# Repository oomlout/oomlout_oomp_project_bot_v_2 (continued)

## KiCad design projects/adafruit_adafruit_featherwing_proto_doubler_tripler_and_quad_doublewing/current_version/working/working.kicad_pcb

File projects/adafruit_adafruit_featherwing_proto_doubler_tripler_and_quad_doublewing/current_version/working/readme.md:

# adafruit_featherwing_proto_doubler_tripler_and_quad
 
## summary 
* id: adafruit_adafruit_featherwing_proto_doubler_tripler_and_quad_doublewing
* user: adafruit
* name: adafruit_featherwing_proto_doubler_tripler_and_quad
* board: doublewing
* repo: https://github.com/adafruit/Adafruit-FeatherWing-Proto-Doubler-Tripler-and-Quad

* src_file_repo_sch: 
* src_file_repo_sch_link: https://github.com/adafruit/Adafruit-FeatherWing-Proto-Doubler-Tripler-and-Quad/tree/master/
* full details link: https://github.com/oomlout/oomlout_oomp_project_bot_v_2/tree/main/projects/adafruit_adafruit_featherwing_proto_doubler_tripler_and_quad_doublewing/current_version/working  

## schematic  
  
[schematic (pdf)](working_schematic.pdf) 

## pcb  

[board (pdf)](working.pdf)  

## working_bom
| Id | Designator | Footprint | Quantity | Designation | Supplier and ref |  | None | 
| --- | --- | --- | --- | --- | --- | --- | --- | 
| 1 | MS1,MS2 | FEATHERWING_DIM | 2 | FEATHERWING_NODIM |  |  | [''] | 
| 2 | JP2,JP3 | 1X16_ROUND_76MIL | 2 |  |  |  | [''] | 
| 3 | JP1,JP4 | 1X12_ROUND_76MIL | 2 |  |  |  | [''] | 

## bom_schematic
| Ref | Qnty | Value | Cmp name | Footprint | Description | Vendor | DNP | 
| --- | --- | --- | --- | --- | --- | --- | --- | 
| JP1, JP4 | 2 | HEADER-1X1276MIL | HEADER-1X1276MIL | working:1X12_ROUND_76MIL |  |  |  | 
| JP2, JP3 | 2 | HEADER-1X16_76MIL | HEADER-1X16_76MIL | working:1X16_ROUND_76MIL |  |  |  | 
| MS1, MS2 | 2 | FEATHERWING_NODIM | FEATHERWING_NODIM | working:FEATHERWING_DIM |  |  |  |

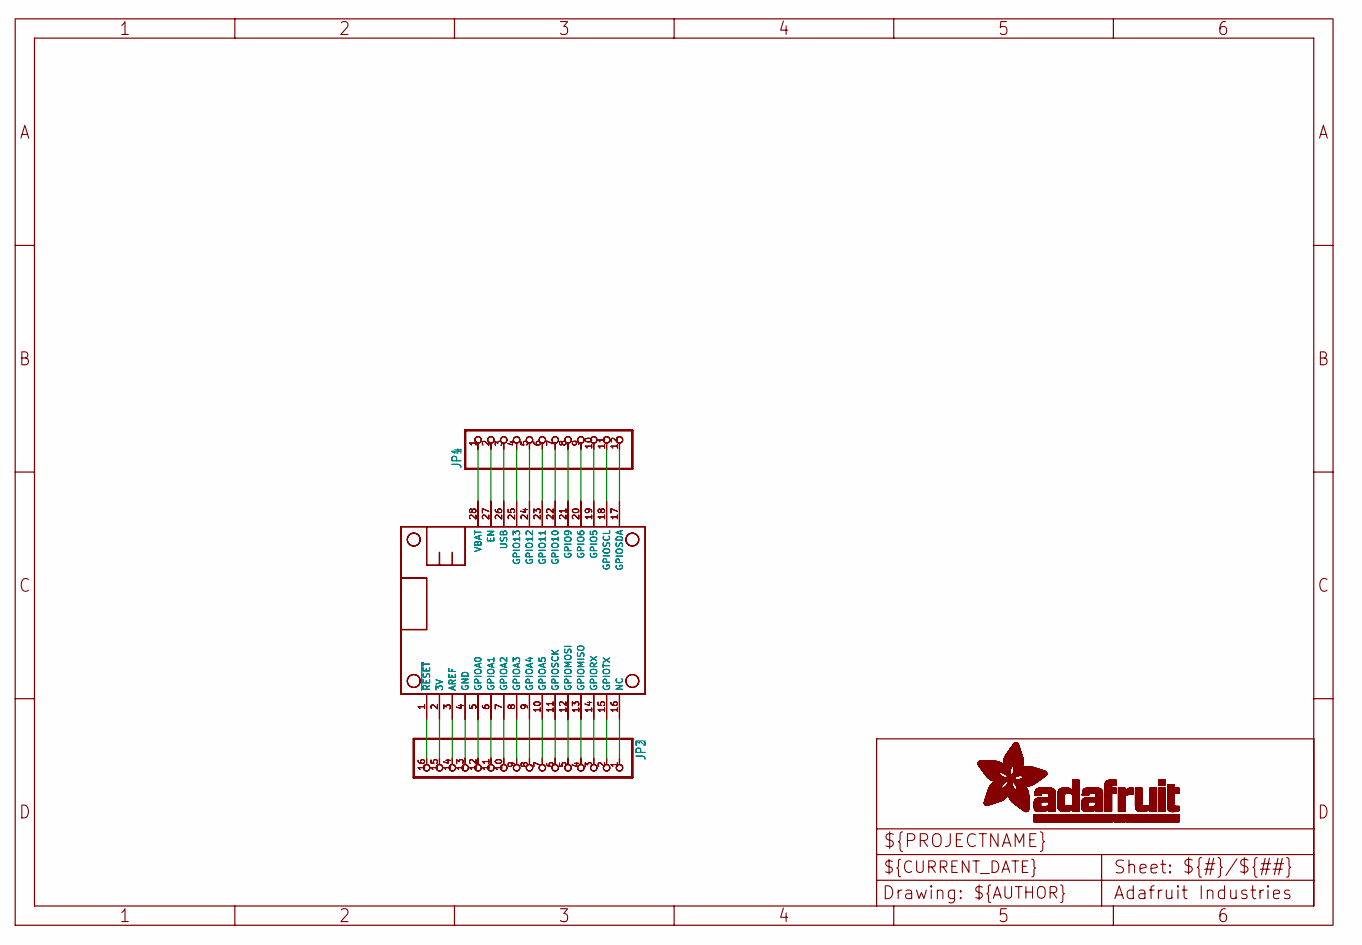
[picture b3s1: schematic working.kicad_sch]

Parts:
JP1, JP4: HEADER-1X1276MIL; 1X12_ROUND_76MIL
JP2, JP3: HEADER-1X16_76MIL; 1X16_ROUND_76MIL
MS1, MS2: FEATHERWING_NODIM; FEATHERWING_DIM

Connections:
3V: JP2.15, JP3.15, MS1.2 (3V), MS2.2 (3V)
GND: JP2.13, JP3.13, MS1.4 (GND), MS2.4 (GND)
unnamed: JP1.2, JP4.2, MS1.27 (EN), MS2.27 (EN)
unnamed: JP2.1, JP3.1, MS1.16 (NC), MS2.16 (NC)
unnamed: JP1.4, JP4.4, MS1.25 (GPIO13), MS2.25 (GPIO13)
unnamed: JP2.2, JP3.2, MS1.15 (GPIOTX), MS2.15 (GPIOTX)
unnamed: JP1.5, JP4.5, MS1.24 (GPIO12), MS2.24 (GPIO12)
unnamed: JP2.3, JP3.3, MS1.14 (GPIORX), MS2.14 (GPIORX)
unnamed: JP2.4, JP3.4, MS1.13 (GPIOMISO), MS2.13 (GPIOMISO)
unnamed: JP2.5, JP3.5, MS1.12 (GPIOMOSI), MS2.12 (GPIOMOSI)
unnamed: JP2.6, JP3.6, MS1.11 (GPIOSCK), MS2.11 (GPIOSCK)
unnamed: JP2.7, JP3.7, MS1.10 (GPIOA5), MS2.10 (GPIOA5)
unnamed: JP2.8, JP3.8, MS1.9 (GPIOA4), MS2.9 (GPIOA4)
unnamed: JP2.9, JP3.9, MS1.8 (GPIOA3), MS2.8 (GPIOA3)
unnamed: JP2.10, JP3.10, MS1.7 (GPIOA2), MS2.7 (GPIOA2)
unnamed: JP2.11, JP3.11, MS1.6 (GPIOA1), MS2.6 (GPIOA1)
unnamed: JP2.12, JP3.12, MS1.5 (GPIOA0), MS2.5 (GPIOA0)
unnamed: JP2.14, JP3.14, MS1.3 (AREF), MS2.3 (AREF)
unnamed: JP2.16, JP3.16, MS1.1 (~RESET), MS2.1 (~RESET)
unnamed: JP1.6, JP4.6, MS1.23 (GPIO11), MS2.23 (GPIO11)
unnamed: JP1.7, JP4.7, MS1.22 (GPIO10), MS2.22 (GPIO10)
unnamed: JP1.8, JP4.8, MS1.21 (GPIO9), MS2.21 (GPIO9)
unnamed: JP1.9, JP4.9, MS1.20 (GPIO6), MS2.20 (GPIO6)
unnamed: JP1.10, JP4.10, MS1.19 (GPIO5), MS2.19 (GPIO5)
unnamed: JP1.11, JP4.11, MS1.18 (GPIOSCL), MS2.18 (GPIOSCL)
unnamed: JP1.12, JP4.12, MS1.17 (GPIOSDA), MS2.17 (GPIOSDA)
USB: JP1.3, JP4.3, MS1.26 (USB), MS2.26 (USB)
VBAT: JP1.1, JP4.1, MS1.28 (VBAT), MS2.28 (VBAT)

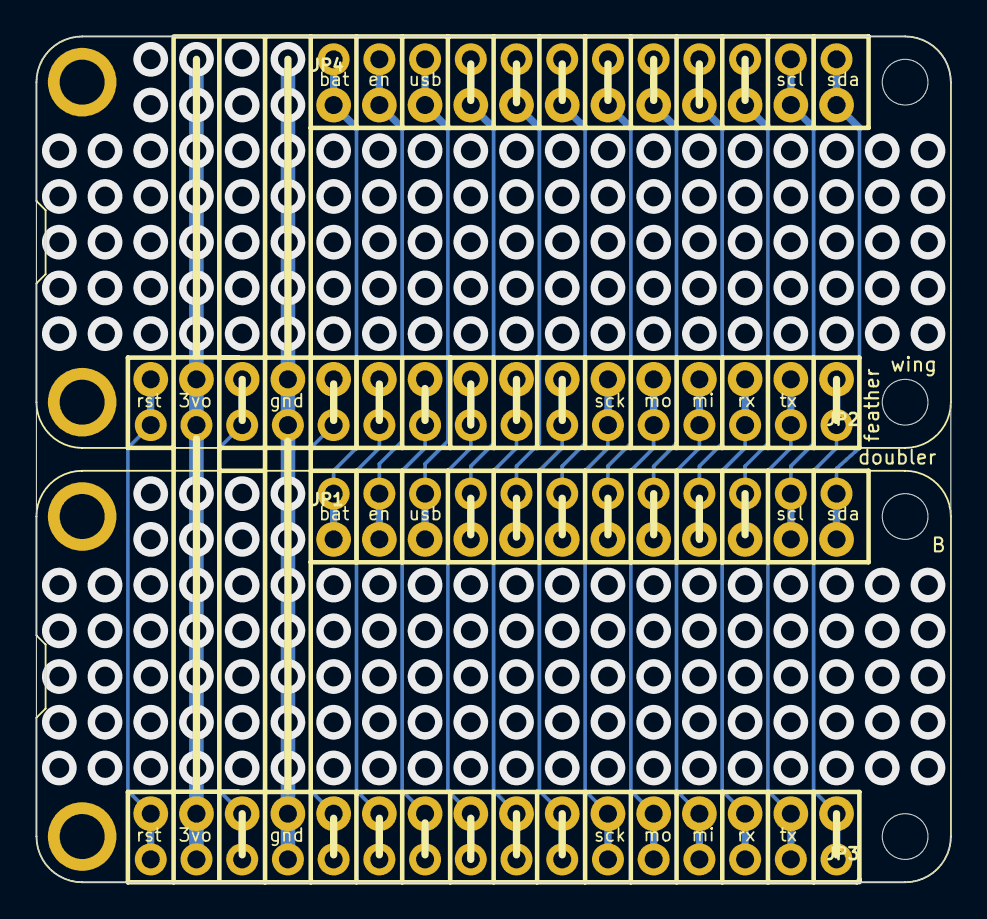
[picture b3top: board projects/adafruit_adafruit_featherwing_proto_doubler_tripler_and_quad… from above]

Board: 2 copper layers, 50.8 x 47.0 mm, 6 parts (0 on the bottom side), 28 nets.
